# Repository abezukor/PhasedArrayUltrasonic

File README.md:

# 2D Phased Array Ultrasonic Transmitter
For details on construction [see the report](Report/Report.md).

# Compilation
First have the [RPI Pico SDK](https://github.com/raspberrypi/pico-sdk) downloaded, and have its path set in the `PICO_SDK_PATH` environment variable.
```bash
mkdir -p Software/build
cd Software/Build
cmake ..
make -j$(($(grep -c ^processor /proc/cpuinfo)-1)) # Compile using all available cores -1.
```

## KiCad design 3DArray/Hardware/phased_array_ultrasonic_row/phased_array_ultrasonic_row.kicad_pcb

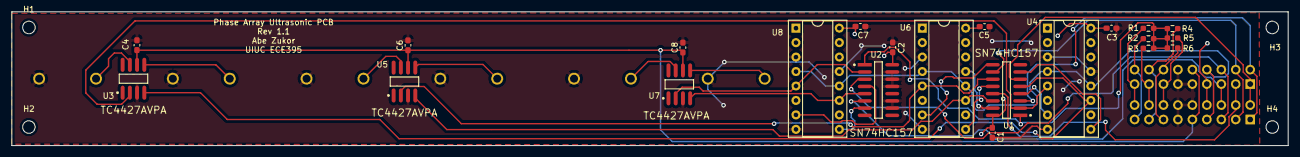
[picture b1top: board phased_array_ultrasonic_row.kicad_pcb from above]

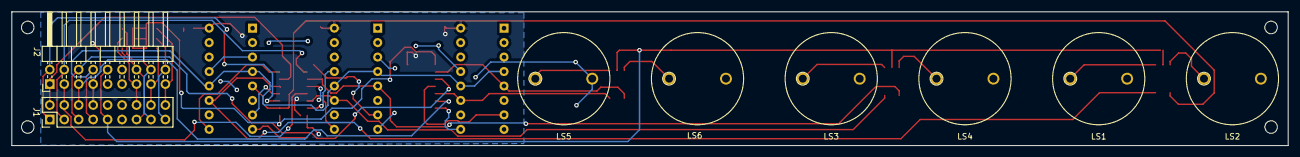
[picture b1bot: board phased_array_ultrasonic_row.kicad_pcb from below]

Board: 2 copper layers, 224.3 x 23.5 mm, 34 parts (8 on the bottom side), 35 nets.

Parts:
C1, C2, C3, C4, C5, C6, C7, C8: 10n; C_0603_1608Metric_Pad1.08x0.95mm_HandSolder
H1, H2, H3, H4: MountingHole; MountingHole_2.2mm_M2
J1: Conn_02x09_Counter_Clockwise; PinHeader_2x09_P2.54mm_Vertical
J2: Conn_02x09_Counter_Clockwise; PinHeader_2x09_P2.54mm_Horizontal
LS1, LS2, LS3, LS4, LS5, LS6: Speaker_Ultrasound; TR40-16
R1, R2, R3, R4, R5, R6: 0; R_0603_1608Metric_Pad0.98x0.95mm_HandSolder
U1, U2: SN74HC157; Texas_Instruments-D0016A-0-0-IPC_A
U3, U5, U7: TC4427AVPA; Microchip-TC4427AEOA713-Level_A
U4, U6, U8: CD4517BE; DIP-16_W7.62mm_Socket

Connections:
3V3: C1.1, C2.1, C3.1, C5.1, C7.1, J1.8, J2.7, U1.16 (VCC), U2.16 (VCC), U4.16 (VDD), U6.16 (VDD), U8.16 (VDD)
18V: C4.1, C6.1, C8.1, J1.9, J2.10, U3.6 (VDD), U5.6 (VDD), U7.6 (VDD)
/C1: J1.1, J2.2, U1.3 (1B)
/C2: J1.2, J2.1, U1.6 (2B)
/C3: J1.3, J2.4, U1.10 (3B)
/C4: J1.4, J2.3, U1.13 (4B)
/C5: J1.5, J2.6, U2.3 (1B)
/C6: J1.6, J2.5, U2.6 (2B)
/CLK: J1.7, J2.8, U4.4 (CLA), U4.12 (CLB), U6.4 (CLA), U6.12 (CLB), U8.4 (CLA), U8.12 (CLB)
/Speakers12/DA: U1.4 (1Y), U4.7 (DA)
/Speakers12/DB: U1.7 (2Y), U4.9 (DB)
/Speakers12/SigA: U1.2 (1A), U3.2 (IN_A), U4.5 (Q64A)
/Speakers12/SigB: U1.5 (2A), U3.4 (IN_B), U4.11 (Q64B)
/Speakers34/DA: U1.9 (3Y), U6.7 (DA)
/Speakers34/DB: U1.12 (4Y), U6.9 (DB)
/Speakers34/SigA: U1.11 (3A), U5.2 (IN_A), U6.5 (Q64A)
/Speakers34/SigB: U1.14 (4A), U5.4 (IN_B), U6.11 (Q64B)
/Speakers56/DA: U2.4 (1Y), U8.7 (DA)
/Speakers56/DB: U2.7 (2Y), U8.9 (DB)
/Speakers56/SigA: U2.2 (1A), U7.2 (IN_A), U8.5 (Q64A)
/Speakers56/SigB: U2.5 (2A), U7.4 (IN_B), U8.11 (Q64B)
/WL1: J1.18, J2.17, R1.2
/WL2: J1.17, J2.18, R2.2
/WL3: J1.16, J2.15, R3.2
/WL4: J1.15, J2.16, R4.2
/WL5: J1.14, J2.13, R5.2
/WL6: J1.13, J2.14, R6.2
/W/L': R1.1, R2.1, R3.1, R4.1, R5.1, R6.1, U1.1 (*A/B), U2.1 (*A/B)
GND: C1.2, C2.2, C3.2, C4.2, C5.2, C6.2, C7.2, C8.2, J1.10, J1.11, J1.12, J2.9, J2.11, J2.12, LS1.2, LS2.2, LS3.2, LS4.2, LS5.2, LS6.2, U1.15 (*G), U2.10 (3B), U2.11 (3A), U2.13 (4B), U2.14 (4A), U2.15 (*G), U3.3 (GND), U4.3 (WEA), U4.8 (VSS), U4.13 (WEB), U5.3 (GND), U6.3 (WEA), U6.8 (VSS), U6.13 (WEB), U7.3 (GND), U8.3 (WEA), U8.8 (VSS), U8.13 (WEB)
unnamed: LS1.1, U3.5 (OUT_B)
unnamed: LS2.1, U3.7 (OUT_A)
unnamed: LS3.1, U5.5 (OUT_B)
unnamed: LS4.1, U5.7 (OUT_A)
unnamed: LS5.1, U7.5 (OUT_B)
unnamed: LS6.1, U7.7 (OUT_A)

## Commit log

2022-09-21 Initial Commit, pio program, 2D ultrasonic math
2022-09-26 Added ADC Code (untested)
2022-09-26 Fixed lots of minor bugs.
2022-10-06 Creating Phases properly. It also may be generating 2d phases correctly but I am stil checking that,
2022-10-31 Row PCB
2023-02-03 Reforatted Repository
2023-02-17 Fixed pcb mux inpits swapped for C6, C6.
2023-02-28 Report Draft 1
2023-02-28 3D Array Should be working. I dont think it is.
2023-03-01 Added alot to the report.
2023-03-03 Report Finished Draft 1
2023-03-03 1D Array Branch
2023-03-03 Repository Reformat 2
2023-03-03 Removed Submodules and copyright message, Added Lisense
2023-03-03 Added README
2023-03-03 Code documentation
